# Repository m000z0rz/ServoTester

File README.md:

# ServoTester
Servo testing device

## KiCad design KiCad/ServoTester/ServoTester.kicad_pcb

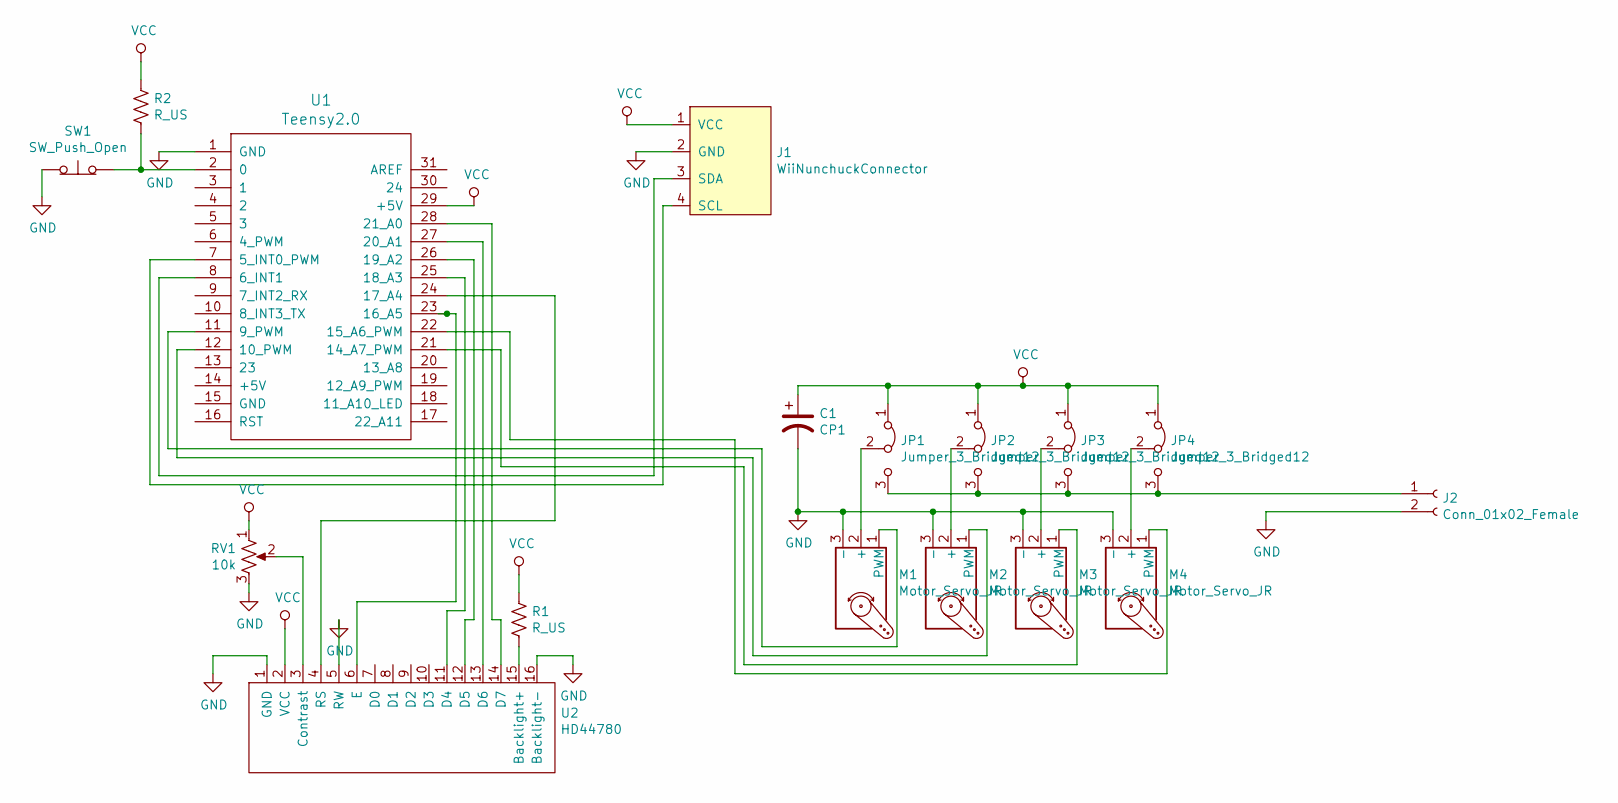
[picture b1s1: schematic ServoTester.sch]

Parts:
C1: CP1; CP_Radial_D8.0mm_P5.00mm
J1: WiiNunchuckConnector
J2: Conn_01x02_Female; BananaJack_2
JP1, JP2, JP3, JP4: Jumper_3_Bridged12; PinHeader_1x03_P2.54mm_Vertical
M1, M2, M3, M4: Motor_Servo_JR; PinHeader_1x03_P2.54mm_Vertical
R1, R2: R_US; R_Axial_DIN0207_L6.3mm_D2.5mm_P10.16mm_Horizontal
RV1: 10k; Potentiometer
SW1: SW_Push_Open; SW_PUSH_6mm_H5mm
U1: Teensy2.0
U2: HD44780; JHD204AO 20x4 Character LCD

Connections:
GND: C1.2, J1.2 (GND), J2.2, M1.3 (-), M2.3 (-), M3.3 (-), M4.3 (-), RV1.3, SW1.1 (A), U1.1 (GND), U2.1 (GND), U2.5 (RW), U2.16 (Backlight-)
unnamed: J1.3 (SDA), U1.8 (6_INT1)
unnamed: J1.4 (SCL), U1.7 (5_INT0_PWM)
unnamed: J2.1, JP1.3 (B), JP2.3 (B), JP3.3 (B), JP4.3 (B)
unnamed: JP1.2 (C), M1.2 (+)
unnamed: JP2.2 (C), M2.2 (+)
unnamed: JP3.2 (C), M3.2 (+)
unnamed: JP4.2 (C), M4.2 (+)
unnamed: M1.1 (PWM), U1.11 (9_PWM)
unnamed: M2.1 (PWM), U1.12 (10_PWM)
unnamed: M3.1 (PWM), U1.21 (14_A7_PWM)
unnamed: M4.1 (PWM), U1.22 (15_A6_PWM)
unnamed: R1.2, U2.15 (Backlight+)
unnamed: R2.2, SW1.2 (B), U1.2 (0)
unnamed: RV1.2, U2.3 (Contrast)
unnamed: U1.23 (16_A5), U2.6 (E)
unnamed: U1.24 (17_A4), U2.4 (RS)
unnamed: U1.25 (18_A3), U2.11 (D4)
unnamed: U1.26 (19_A2), U2.12 (D5)
unnamed: U1.27 (20_A1), U2.13 (D6)
unnamed: U1.28 (21_A0), U2.14 (D7)
VCC: C1.1, J1.1 (VCC), JP1.1 (A), JP2.1 (A), JP3.1 (A), JP4.1 (A), R1.1, R2.1, RV1.1, U1.29 (+5V), U2.2 (VCC)

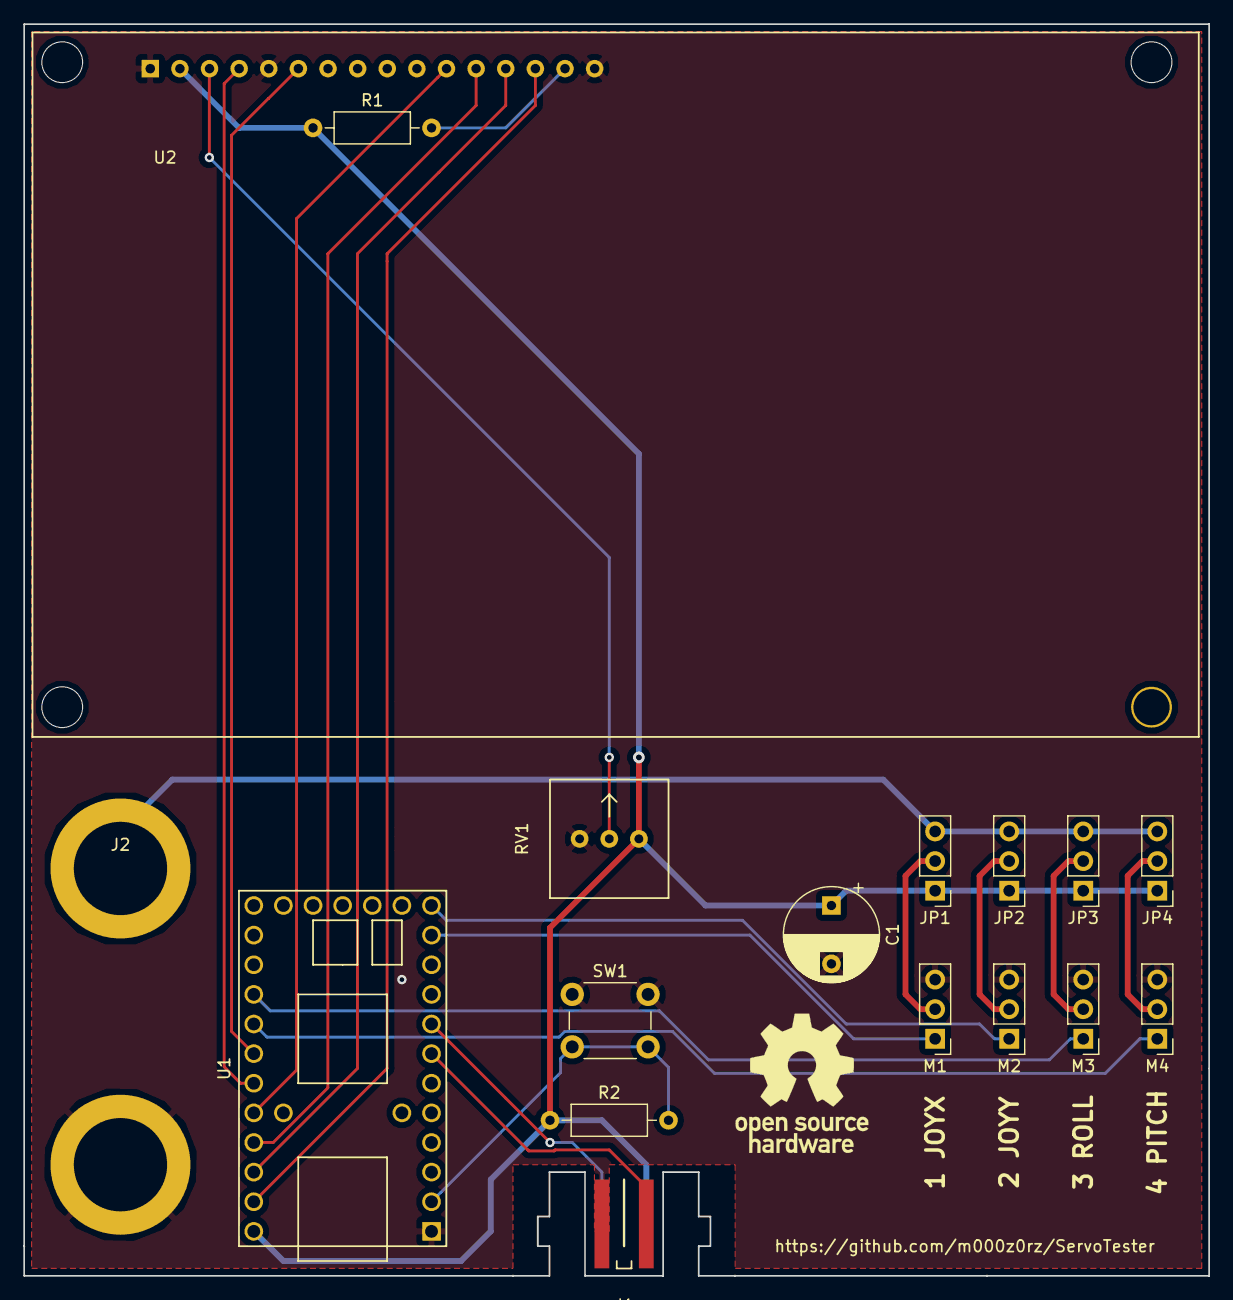
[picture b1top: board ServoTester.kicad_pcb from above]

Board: 2 copper layers, 101.6 x 107.3 mm, 17 parts (0 on the bottom side), 22 nets.

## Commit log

2019-07-11 in progress
2019-07-12 working on board
2019-07-14 think board is ready for prototyping
2019-07-15 board labels, and software: don't require stick movement for save, notify saved on lcd, fix deg<->pms conversion, ...
2019-09-11 fixing board
